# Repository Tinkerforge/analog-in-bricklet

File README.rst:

Analog In Bricklet
==================

This repository contains the firmware source code and the hardware design
files. The documentation generator configs can be found at
https://github.com/Tinkerforge/generators

Repository Content
------------------

software/:
 * examples/: Examples for all supported languages
 * build/: Compiled files
 * src/: Source code of firmware
 * Makefile: Makefile to build project

hardware/:
 * Contains KiCad project files and additionally schematics as PDF

datasheets/:
 * Contains datasheets for sensors and complex ICs that are used

Hardware
--------

The hardware is designed with the open source EDA Suite KiCad
(http://www.kicad.org). Before you are able to open the files,
you have to install the Tinkerforge kicad-libraries
(https://github.com/Tinkerforge/kicad-libraries). You can either clone
them directly in hardware/ or clone them in a separate folder and
symlink them into hardware/
(ln -s kicad_path/kicad-libraries project_path/hardware). After that you
can open the .pro file in hardware/ with KiCad and from there view and
modify the schematics and the PCB layout.

Software
--------

If you want to do your own Brick/Bricklet firmware development we highly
recommend that you use our build environment setup script and read the
tutorial (https://www.tinkerforge.com/en/doc/Tutorials/Tutorial_Build_Environment/Tutorial.html).

To compile the C code we recommend you to install the newest GNU Arm Embedded
Toolchain (https://launchpad.net/gcc-arm-embedded/+download).
You also need to install bricklib (https://github.com/Tinkerforge/bricklib)
and brickletlib (https://github.com/Tinkerforge/brickletlib).

You can either clone it directly in software/src/ or clone it in a
separate folder and symlink it into software/src/
(ln -s bricklib_path/bricklib project_path/software/src/ and
ln -s brickletlib_path/brickletlib project_path/software/src/).
Finally make sure to have CMake installed
(http://www.cmake.org/cmake/resources/software.html).

After that you can build the firmware by invoking make in software/.
The firmware (.bin) can then be found in software/build/ and uploaded
with brickv (click button "Flashing" on start screen).

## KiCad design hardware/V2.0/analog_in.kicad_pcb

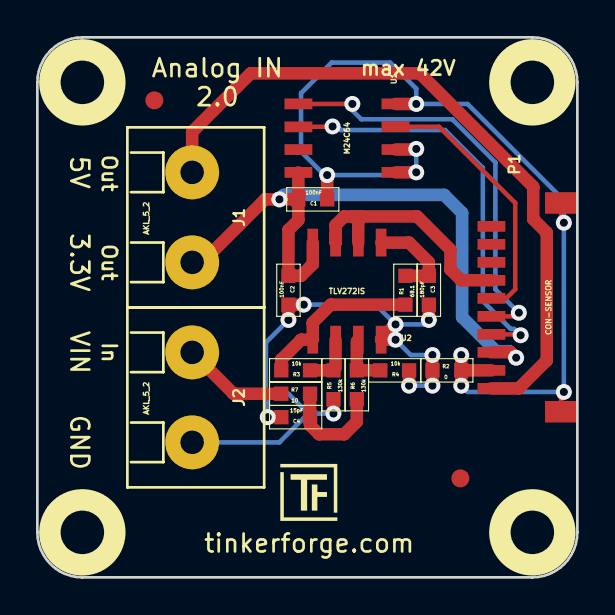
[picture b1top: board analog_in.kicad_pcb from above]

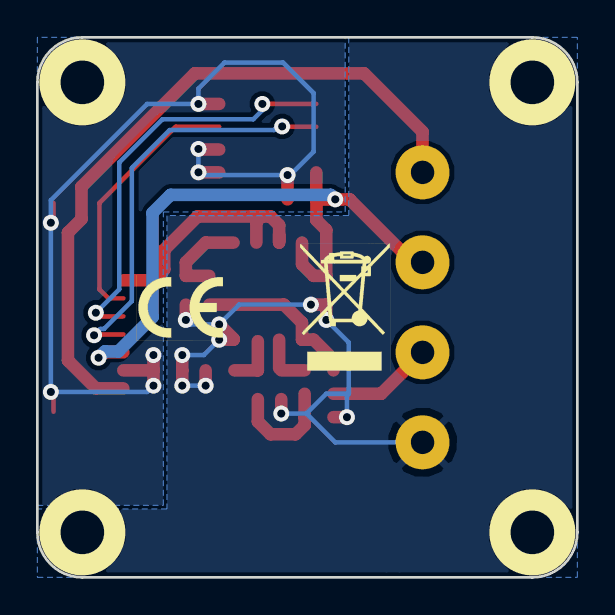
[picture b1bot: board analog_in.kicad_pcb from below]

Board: 2 copper layers, 30.0 x 30.0 mm, 24 parts (2 on the bottom side), 14 nets.

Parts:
C1, C2: 100nF; 0603
C3: 180pF; 0603
C4: 15pF; 0603
Fiducial_Mark: VAL**; Fiducial_Mark
Fiducial_Mark#2: VAL**; Fiducial_Mark
J1, J2: AKL_5_2
P1: CON-SENSOR
R1: 68.1; 0603
R2: 0; 0603
R3, R4: 10k; 0603
R5, R6: 130k; 0603
R7: 10; 0603
U1: M24C64; SOIC8
U2: TLV272IS; SOIC8
U3, U4, U5, U6: DRILL; DRILL_NP
VAL: CE_5mm
VAL#2: WEEE_7mm

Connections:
3V3: C1.1, C2.2, J1.1, P1.3, U1.8, U2.8
+5V: J1.2, P1.1
ADC0: C3.2, R1.1, U2.5
AGND: C2.1, C3.1, C4.1, J2.1, R2.2, R4.2, R5.2, U2.4
GND: C1.2, P1.2, P1.EP, R2.1, U1.1, U1.2, U1.4
unnamed: C4.2, R6.2, R7.1
unnamed: J2.2, R7.2
unnamed: P1.4, U1.6
unnamed: P1.5, U1.5
unnamed: P1.6, U1.3
unnamed: P1.7, U2.6, U2.7
unnamed: R1.2, R3.1, U2.1
unnamed: R3.2, R5.1, U2.2
unnamed: R4.1, R6.1, U2.3

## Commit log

2012-02-15 hardware check in of analog in bricklet version 1.0
2012-02-15 remove debug output, add changelog
2012-02-15 Move software changelog to software folder
2012-03-09 Remove smallest resolution for now, to prevent high voltages if nothing is connected
2012-04-25 Unify capitalization of "IP connection" in examples
2012-05-09 Add PHP examples
2012-05-14 Remove stray Java class files
2012-05-14 java: Remove unnecessary new String(...) calls
2012-05-25 Add Ruby examples
2012-06-05 Fix register_callback syntax error in Ruby examples on Windows
2012-06-12 Use correct term 'Bricklet' in example code error message
2012-06-12 Prefer IPConnection destroy over join_thread
2012-07-01 Add generate_makefile.bat for windows
2012-07-25 Add Delphi examples
2012-08-08 delphi: Add comment about UID
2012-09-28 Remove accidentially commited files
2012-10-24 Make cmake find the correct objcopy binary
    On some systems cmake uses the wrong objcopy binary, tell it to use
    the correct one.
2012-11-13 Support for protocol 2.0
2012-11-28 Make python examples protocol 2.0 compatible
2012-11-29 Make Ruby examples Protocol 2.0 compatible
2012-11-29 Make C examples Protocol 2.0 compatible
2012-11-29 Make Java examples Protocol 2.0 compatible
2012-11-29 Make PHP examples Protocol 2.0 compatible
2012-11-29 Make Delpho/Pascal examples Protocol 2.0 compatible
2012-11-30 delphi: Remove unnecessary parentheses and call destructor again
2012-12-05 Add protocol 2.0 compatability to C# bindings
2012-12-06 Fix C examples
2012-12-11 Avoid g++ warnings about missing casts in C examples
2012-12-21 Add .gitignore
2013-01-09 Use specific device object for callbacks
2013-01-17 Make Java examples compatible to new listener approach
2013-01-28 Update outdated comment in Java example
2013-02-07 Use IPconnection disconnect explicitly in examples
2013-02-14 Fix debounce period in C# threshold example
2013-02-18 Add Visual Basic .NET examples
2013-02-22 Support manual measurement range selection
2013-05-15 Don't send threshold callback twice
    Fixed in brickletlib.
2013-08-08 Add shell examples
2013-08-21 windows: Don't trigger a build in generate_makefile.bat
    Also use normal make instead of the speical named one.
2013-08-27 Fix jumps in average value calculation due to range switches
    Use a different tick for average value calculation that only updates
    if the average value sum was also updated.
2013-08-28 Add support for 3.3V range
2013-08-28 Add support for changing the averaging length
2013-12-19 Fix wrong length for GetDebounce packet (through brickletlib)
2014-01-06 Add static assert for BrickContext size
2014-01-10 Add Perl examples
2014-01-15 php: Use const for constant values
2014-02-07 Add Mathematica examples
2014-02-10 perl: fixed namespace
2014-02-11 javascript: add examples
2014-02-18 javascript: examples fixed
2014-02-20 javascript: add html examples
2014-02-24 javascript: port 4280, startExample()
2014-02-28 javascript: Break long lines and cleanup whitespace
2014-03-05 Add LabVIEW examples
2014-03-06 labview: Add examples in LV2010 format
2014-03-25 matlab: add examples
2014-04-02 java: Unify constants style
2014-04-02 perl: Unify print style
2014-04-17 matlab: Adapt examples to new callback style
2014-04-17 matlab: Add parentheses to make pygments happy
2014-07-15 java: Replace System.console() usage with an Eclipse compatible pattern
2014-12-02 Use ReadLine instead of ReadKey for C# example
2015-02-13 vbnet: Use ReadLine instead of ReadKey
    Because ReadKey doesn't work with a pipe as stdin on the RED Brick.
2015-03-02 windows: Stop cmake from searching for mingw32-make.exe
    Using MinGW Makefiles as generator makes cmake search for mingw32-make.exe
    which might not be installed because GnuWin32's make.exe is used instead.
2015-03-26 add hardware files for V2.0 prototype
2015-03-31 changed to 5 connector design fuses added for voltage output
2015-04-02 hardware files now in analog-in-v2-bricklet git
2015-04-09 c: Whitespace
2015-06-24 javascript: Clean up output creation
2015-07-23 Make JavaScript browser example textarea readonly
2015-07-27 Cleanup C/C++, C#, Java, Python and Ruby examples
2015-07-29 Reformat changelog
2015-08-07 Use full device class name in Python examples
2015-08-12 Fix minor warnings in C/C++ examples
2015-08-13 Revert accidentally commited changes.
    Added in commit 81f9667b9e7743b6f505e698b8d71551733bc0c5.
2015-08-13 Use correct simple value type to fix threshold value range
2015-08-14 Fix threshold value type in Java example
2015-08-14 Cleanup Delphi examples
2015-08-18 Cleanup VB.NET examples
2015-08-19 Cleanup Perl examples
2015-09-09 Duplicate cmake call to fix bug during cmake creation
2015-09-30 Generator based example cleanup
2015-11-12 matlab: Fix callback handling for R2014a
    http://undocumentedmatlab.com/blog/matlab-callbacks-for-java-events-in-r2014a
2015-11-25 Include date and commit into changelog
2016-05-18 c: Add missing device destroy call
2016-07-01 Make the change UID comment more explicit
2017-04-13 csharp: Adapt example
2017-04-21 shell: Adapt example
2017-06-02 octave: Use javaObject instead of deprecated java_new
2017-11-30 Update examples from generator
2017-12-07 mathematica: Also generate .nb files
2018-01-30 Update examples
2018-02-19 javascript: Close div tag correctly
2018-02-20 Cleanup KiCad libraries config
    Ensure LibDir=kicad-libraries and LibName1=tinkerforge.
    Remove special library.
2018-05-24 perl: Use strict in examples
2018-07-11 Add Makefile with docker support
2018-07-11 Update directory structure and build instructions
2018-07-11 Remove obsolete generate_makefile scripts
2018-11-06 Add rust examples
2018-11-07 rust: Accept host names for ip connection, fix naming inconsistencies
2018-11-07 rust: Rename callback receivers.
2018-12-14 Add go examples.
2018-12-14 go: Fix printf parameters.
2018-12-18 go: Change import path.
2018-12-18 go: Change import path again.
2018-12-20 rust: Reformat examples.
2019-01-24 mqtt: Add examples.
2019-01-24 mqtt: Fix example header.
2019-01-24 mqtt: Remove executable bit in example permissions.
2019-01-24 go: Minor example fixes.
2019-01-24 mqtt: Minor example fixes.
2019-03-28 mqtt: Fix whitespace.
2019-08-22 c: Adapt to bindings changes
2020-01-13 examples: Use python3 input instead of python2 raw_input.
2020-01-13 examples: mqtt: Remove trailing whitespace.
2020-04-14 mqtt: Fix device name format
2021-10-25 Update KiCad link
    https://www.kicad.org/blog/2021/10/Avoid-links-to-former-kicad-domain/
2022-07-06 Add license files.

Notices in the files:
hardware/V2.0/analog_in.kicad_pcb:
Licensed under CERN OHL v.1.1
Copyright (©) 2015, B.Nordmeyer
Copyright Tinkerforge GmbH 2015.
This documentation describes Open Hardware and is licensed under the
CERN OHL v. 1.1.
